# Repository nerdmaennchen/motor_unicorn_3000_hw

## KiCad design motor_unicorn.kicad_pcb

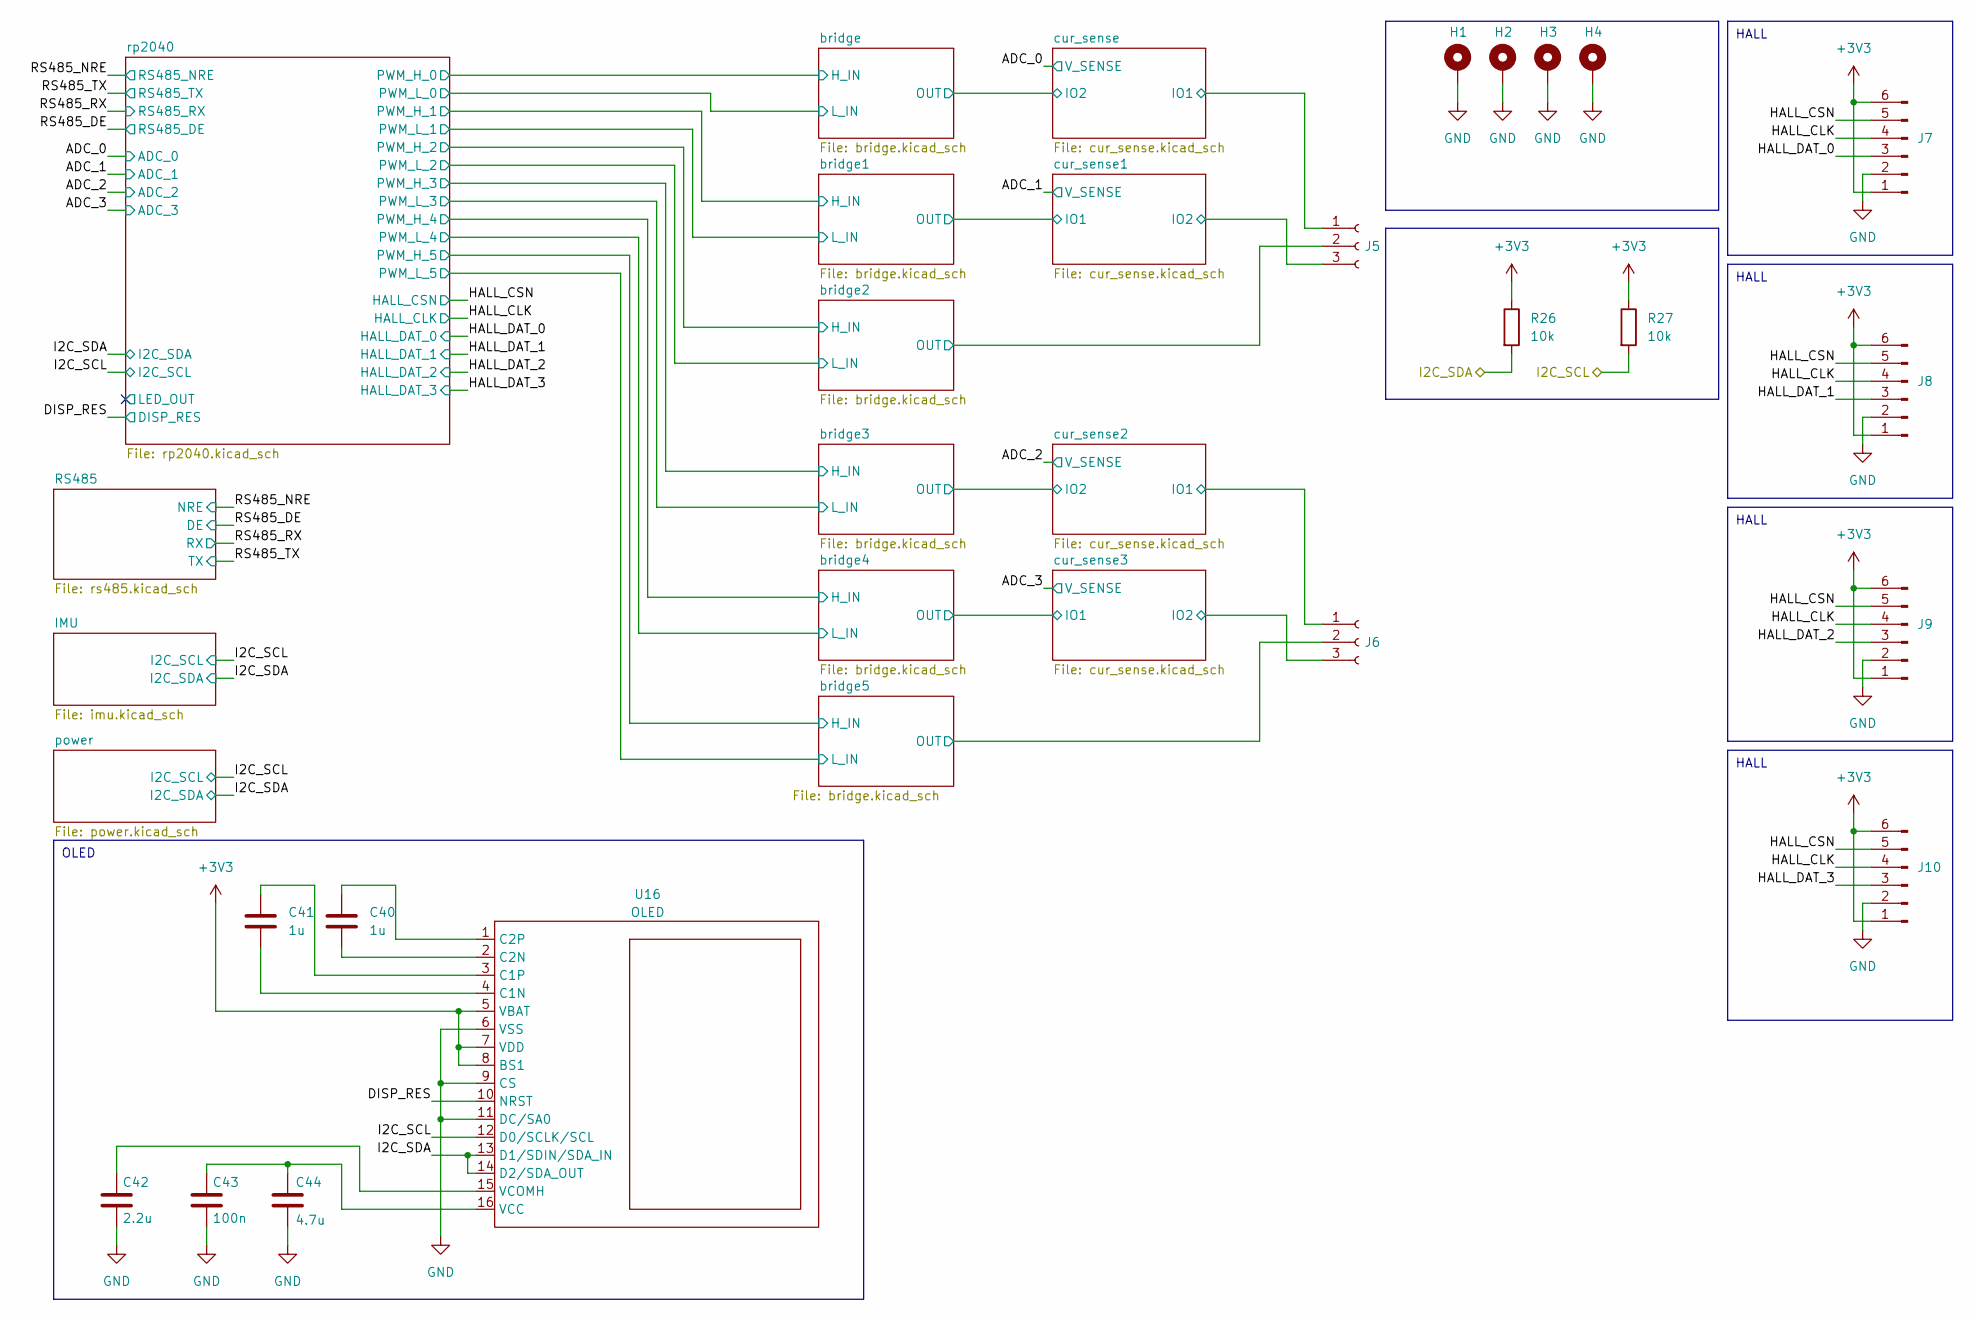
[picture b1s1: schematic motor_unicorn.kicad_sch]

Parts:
C40, C41: 1u; C_0402_1005Metric; LCSC C52923
C42: 2.2u; C_0805_2012Metric; LCSC C12530
C43: 100n; C_0402_1005Metric; LCSC C1525
C44: 4.7u; C_0603_1608Metric; LCSC C19666
H1, H2, H3, H4: MountingHole_Pad; MountingHole_3.2mm_M3_DIN965_Pad_TopBottom
J5, J6: Conn_01x03_Socket; TerminalBlock_Altech_AK300-3_P5.00mm; LCSC C8270
J7, J8, J9, J10: Conn_01x06_Pin; JST_PH_B6B-PH-K_1x06_P2.00mm_Vertical; LCSC C131342
R26, R27: 10k; R_0402_1005Metric; LCSC C25744
U16: OLED

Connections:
+3V3: J7.1, J7.6, J8.1, J8.6, J9.1, J9.6, J10.1, J10.6, R26.1, R27.1, U16.5 (VBAT), U16.7 (VDD), U16.8 (BS1); also elsewhere on the board
/DISP_RES: U16.10 (NRST); also elsewhere on the board
/HALL_CLK: J7.4, J8.4, J9.4, J10.4; also elsewhere on the board
/HALL_CSN: J7.5, J8.5, J9.5, J10.5; also elsewhere on the board
/HALL_DAT_0: J7.3; also elsewhere on the board
/HALL_DAT_1: J8.3; also elsewhere on the board
/HALL_DAT_2: J9.3; also elsewhere on the board
/HALL_DAT_3: J10.3; also elsewhere on the board
/I2C_SCL: R27.2, U16.12 (D0/SCLK/SCL); also elsewhere on the board
/I2C_SDA: R26.2, U16.13 (D1/SDIN/SDA_IN), U16.14 (D2/SDA_OUT); also elsewhere on the board
/bridge2/OUT: J5.2; also elsewhere on the board
/bridge5/OUT: J6.2; also elsewhere on the board
/cur_sense1/IO2: J5.3; also elsewhere on the board
/cur_sense2/IO1: J6.1; also elsewhere on the board
/cur_sense3/IO2: J6.3; also elsewhere on the board
/cur_sense/IO1: J5.1; also elsewhere on the board
GND: C42.2, C43.2, C44.2, H1.1, H2.1, H3.1, H4.1, J7.2, J8.2, J9.2, J10.2, U16.6 (VSS), U16.9 (CS), U16.11 (DC/SA0); also elsewhere on the board
unnamed: C41.2, U16.4 (C1N)
unnamed: C41.1, U16.3 (C1P)
unnamed: C40.2, U16.2 (C2N)
unnamed: C40.1, U16.1 (C2P)
unnamed: C43.1, C44.1, U16.16 (VCC)
unnamed: C42.1, U16.15 (VCOMH)

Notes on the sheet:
HALL
OLED

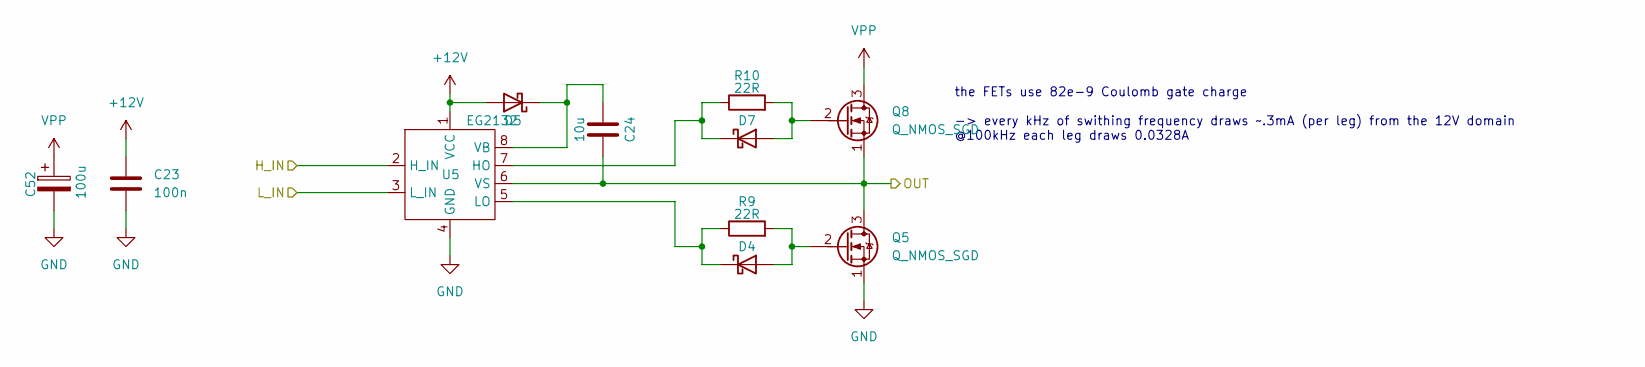
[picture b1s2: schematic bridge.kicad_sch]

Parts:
C23: 100n; C_0402_1005Metric
C24: 10u; C_0603_1608Metric
C52: 100u; CP_Elec_6.3x7.7
D4, D5, D7: D_Schottky; D_SOD-323
Q5, Q8: Q_NMOS_SGD; PQFN-8-EP_6x5mm_P1.27mm_Generic
R9, R10: 22R; R_0402_1005Metric
U5: EG2132; SSOP-8_3.9x5.05mm_P1.27mm

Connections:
+12V: C23.1, D5.2 (A), U5.1 (VCC); also elsewhere on the board
/bridge1/H_IN: U5.2 (H_IN); also elsewhere on the board
/bridge1/L_IN: U5.3 (L_IN); also elsewhere on the board
GND: C23.2, C52.2, Q5.1 (S), U5.4 (GND); also elsewhere on the board
unnamed: D7.1 (K), R10.1, U5.7 (HO)
VPP: C52.1, Q8.3 (D); also elsewhere on the board

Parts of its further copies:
C21, C26, C33, C35, C37: 10u; C_0603_1608Metric
C22, C25, C32, C34, C36: 100n; C_0402_1005Metric
C53, C54, C55, C56, C57: 100u; CP_Elec_6.3x7.7
D3, D6, D8, D9, D10, D11, D12, D13, D14, D15, D16, D17, D18, D19, D20: D_Schottky; D_SOD-323
Q2, Q3, Q4, Q6, Q7, Q9, Q10, Q11, Q12, Q13: Q_NMOS_SGD; PQFN-8-EP_6x5mm_P1.27mm_Generic
R8, R11, R12, R13, R18, R19, R20, R21, R22, R23: 22R; R_0402_1005Metric
U4, U6, U11, U12, U13: EG2132; SSOP-8_3.9x5.05mm_P1.27mm

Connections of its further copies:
+12V: C22.1, C25.1, C32.1, C34.1, C36.1, D6.2 (A), D9.2 (A), D12.2 (A), D15.2 (A), D18.2 (A), U4.1 (VCC), U6.1 (VCC), U11.1 (VCC), U12.1 (VCC), U13.1 (VCC); also elsewhere on the board
/bridge2/H_IN: U6.2 (H_IN); also elsewhere on the board
/bridge2/L_IN: U6.3 (L_IN); also elsewhere on the board
/bridge2/OUT: C26.1, Q4.3 (D), Q10.1 (S), U6.6 (VS); also elsewhere on the board
/bridge3/H_IN: U11.2 (H_IN); also elsewhere on the board
/bridge3/L_IN: U11.3 (L_IN); also elsewhere on the board
/bridge4/H_IN: U12.2 (H_IN); also elsewhere on the board
/bridge4/L_IN: U12.3 (L_IN); also elsewhere on the board
/bridge4/OUT: C35.1, Q6.3 (D), Q12.1 (S), U12.6 (VS); also elsewhere on the board
/bridge5/H_IN: U13.2 (H_IN); also elsewhere on the board
/bridge5/L_IN: U13.3 (L_IN); also elsewhere on the board
/bridge5/OUT: C37.1, Q7.3 (D), Q13.1 (S), U13.6 (VS); also elsewhere on the board
/bridge/H_IN: U4.2 (H_IN); also elsewhere on the board
/bridge/L_IN: U4.3 (L_IN); also elsewhere on the board
GND: C22.2, C25.2, C32.2, C34.2, C36.2, C53.2, C54.2, C55.2, C56.2, C57.2, Q2.1 (S), Q3.1 (S), Q4.1 (S), Q6.1 (S), Q7.1 (S), U4.4 (GND), U6.4 (GND), U11.4 (GND), U12.4 (GND), U13.4 (GND); also elsewhere on the board
unnamed: D3.1 (K), R8.1, U4.7 (HO)
unnamed: D8.2 (A), Q3.2 (G), R11.2
unnamed: C26.2, D9.1 (K), U6.8 (VB)
unnamed: D10.2 (A), Q10.2 (G), R12.2
unnamed: D10.1 (K), R12.1, U6.7 (HO)
unnamed: D11.2 (A), Q4.2 (G), R13.2
unnamed: D11.1 (K), R13.1, U6.5 (LO)
unnamed: C33.2, D12.1 (K), U11.8 (VB)
unnamed: D13.2 (A), Q11.2 (G), R18.2
unnamed: D13.1 (K), R18.1, U11.7 (HO)
unnamed: D14.1 (K), R19.1, U11.5 (LO)
unnamed: C35.2, D15.1 (K), U12.8 (VB)
unnamed: D16.2 (A), Q12.2 (G), R20.2
unnamed: D16.1 (K), R20.1, U12.7 (HO)
unnamed: D17.2 (A), Q6.2 (G), R21.2
unnamed: D17.1 (K), R21.1, U12.5 (LO)
unnamed: C37.2, D18.1 (K), U13.8 (VB)
unnamed: D19.2 (A), Q13.2 (G), R22.2
unnamed: D19.1 (K), R22.1, U13.7 (HO)
unnamed: D20.2 (A), Q7.2 (G), R23.2
unnamed: D20.1 (K), R23.1, U13.5 (LO)
VPP: C53.1, C54.1, C55.1, C56.1, C57.1, Q9.3 (D), Q10.3 (D), Q11.3 (D), Q12.3 (D), Q13.3 (D); also elsewhere on the board

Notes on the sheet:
the FETs use 82e-9 Coulomb gate charge -> every kHz of swithing frequency draws ~.3mA (per leg) from the 12V domain @100kHz each leg draws 0.0328A

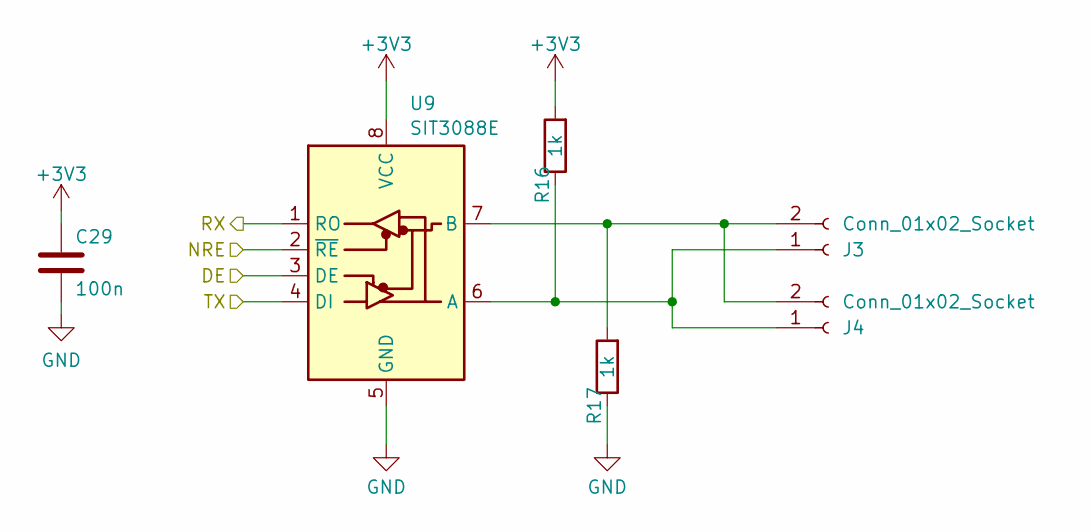
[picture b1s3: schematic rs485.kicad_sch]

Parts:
C29: 100n; C_0402_1005Metric
J3: Conn_01x02_Socket; Molex_PicoBlade_53398-0271_1x02-1MP_P1.25mm_Vertical; LCSC C395343
J4: Conn_01x02_Socket; Molex_PicoBlade_53398-0271_1x02-1MP_P1.25mm_Vertical
R16, R17: 1k; R_0402_1005Metric
U9: SIT3088E; DFN8-3x3mm

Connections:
+3V3: C29.1, R16.2, U9.8 (VCC); also elsewhere on the board
/RS485_DE: U9.3 (DE); also elsewhere on the board
/RS485_NRE: U9.2 (~RE); also elsewhere on the board
/RS485_RX: U9.1 (RO); also elsewhere on the board
/RS485_TX: U9.4 (DI); also elsewhere on the board
GND: C29.2, R17.1, U9.5 (GND); also elsewhere on the board
unnamed: J3.1, J4.1, R16.1, U9.6 (A)
unnamed: J3.2, J4.2, R17.2, U9.7 (B)

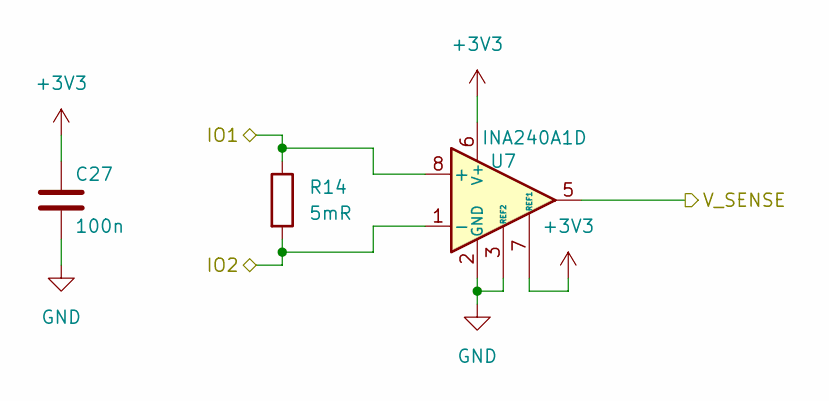
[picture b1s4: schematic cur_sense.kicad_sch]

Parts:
C27: 100n; C_0402_1005Metric
R14: 5mR; R_2512_6332Metric
U7: INA240A1D; SOIC-8_3.9x4.9mm_P1.27mm

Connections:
+3V3: C27.1, U7.6 (V+), U7.7 (REF1); also elsewhere on the board
/ADC_0: U7.5; also elsewhere on the board
/cur_sense/IO1: R14.1, U7.8 (+); also elsewhere on the board
GND: C27.2, U7.2 (GND), U7.3 (REF2), U7.4 (GND); also elsewhere on the board

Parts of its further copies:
C28, C38, C39: 100n; C_0402_1005Metric
R15, R24, R25: 5mR; R_2512_6332Metric
U8, U14, U15: INA240A1D; SOIC-8_3.9x4.9mm_P1.27mm

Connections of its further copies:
+3V3: C28.1, C38.1, C39.1, U8.6 (V+), U8.7 (REF1), U14.6 (V+), U14.7 (REF1), U15.6 (V+), U15.7 (REF1); also elsewhere on the board
/ADC_1: U8.5; also elsewhere on the board
/ADC_2: U14.5; also elsewhere on the board
/ADC_3: U15.5; also elsewhere on the board
/bridge4/OUT: R25.1, U15.8 (+); also elsewhere on the board
/cur_sense1/IO2: R15.2, U8.1 (-); also elsewhere on the board
/cur_sense2/IO1: R24.1, U14.8 (+); also elsewhere on the board
/cur_sense3/IO2: R25.2, U15.1 (-); also elsewhere on the board
GND: C28.2, C38.2, C39.2, U8.2 (GND), U8.3 (REF2), U8.4 (GND), U14.2 (GND), U14.3 (REF2), U14.4 (GND), U15.2 (GND), U15.3 (REF2), U15.4 (GND); also elsewhere on the board

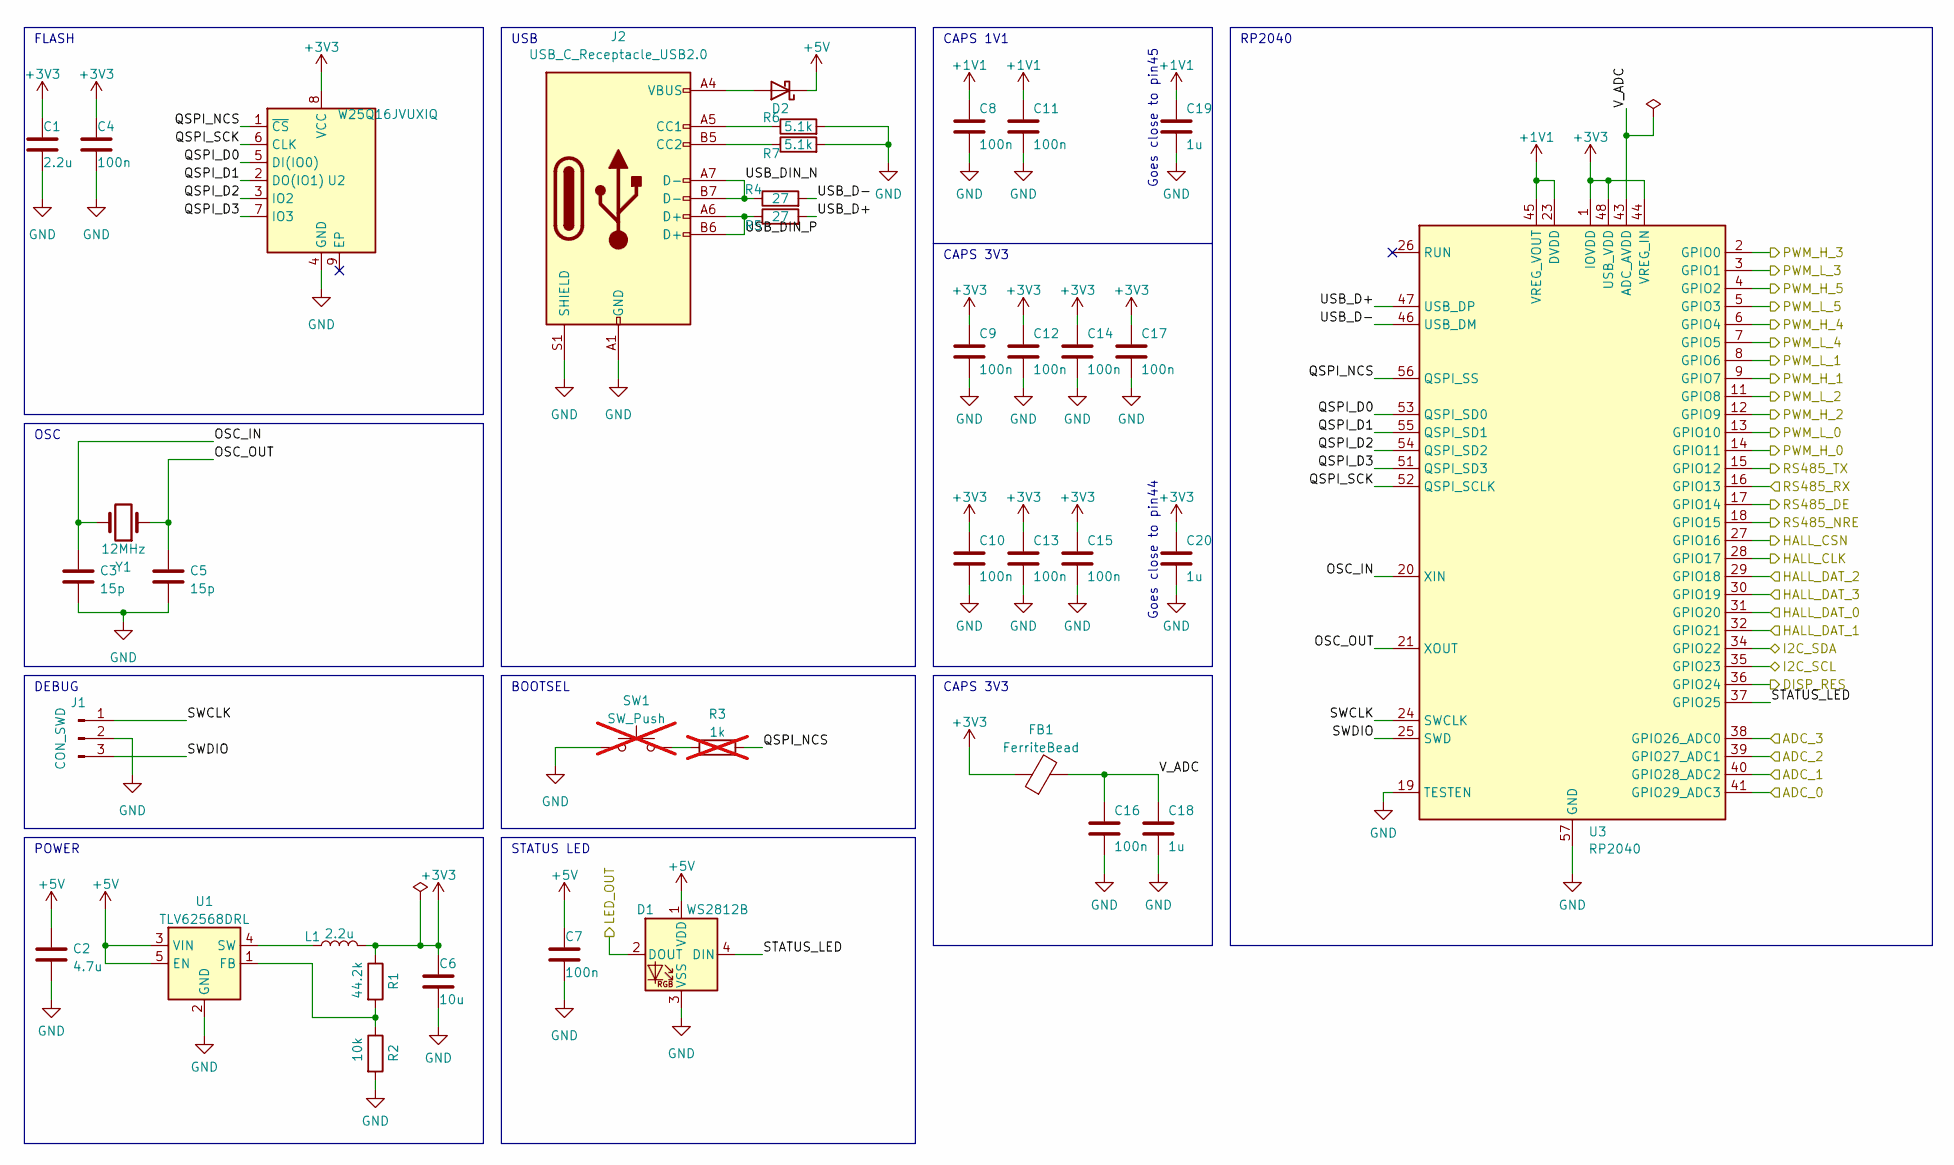
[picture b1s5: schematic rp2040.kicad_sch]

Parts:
C1: 2.2u; C_0402_1005Metric
C2: 4.7u; C_0603_1608Metric
C3, C5: 15p; C_0402_1005Metric
C4, C7, C8, C9, C10, C11, C12, C13, C14, C15, C16, C17: 100n; C_0402_1005Metric
C6: 10u; C_0603_1608Metric
C18, C19, C20: 1u; C_0402_1005Metric
D1: WS2812B; XL-1010RGBC-WS2812B
D2: D_Schottky; D_SOD-323
FB1: FerriteBead; L_0603_1608Metric
J1: CON_SWD; JST_SH_BM03B-SRSS-TB_1x03-1MP_P1.00mm_Vertical
J2: USB_C_Receptacle_USB2.0; USB_C_Receptacle_XKB_U262-16XN-4BVC11
L1: 2.2u; L_0603_1608Metric
R1: 44.2k; R_0402_1005Metric
R2: 10k; R_0402_1005Metric
R3: 1k; R_0402_1005Metric; not fitted
R4, R5: 27; R_0402_1005Metric
R6, R7: 5.1k; R_0402_1005Metric
SW1: SW_Push; SW_Push_1P1T_NO_Vertical_Wuerth_434133025816; not fitted
U1: TLV62568DRL; SOT-563
U2: W25Q16JVUXIQ; DFN-8-1EP_3x2mm_P0.5mm_EP1.3x1.5mm
U3: RP2040; QFN-56-1EP_7x7mm_P0.4mm_EP3.2x3.2mm
Y1: 12MHz; Crystal_SMD_3225-4Pin_3.2x2.5mm

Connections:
+1V1: C8.1, C11.1, C19.1, U3.23 (DVDD), U3.45 (VREG_VOUT), U3.50 (DVDD)
+3V3: C1.1, C4.1, C6.1, C9.1, C10.1, C12.1, C13.1, C14.1, C15.1, C17.1, C20.1, FB1.1, L1.2, R1.1, U2.8 (VCC), U3.1 (IOVDD), U3.10 (IOVDD), U3.22 (IOVDD), U3.33 (IOVDD), U3.42 (IOVDD), U3.44 (VREG_IN), U3.48 (USB_VDD), U3.49 (IOVDD); also elsewhere on the board
+5V: C2.1, C7.1, D1.1 (VDD), D2.1 (K), U1.3 (VIN), U1.5 (EN); also elsewhere on the board
/ADC_0: U3.41 (GPIO29_ADC3); also elsewhere on the board
/ADC_1: U3.40 (GPIO28_ADC2); also elsewhere on the board
/ADC_2: U3.39 (GPIO27_ADC1); also elsewhere on the board
/ADC_3: U3.38 (GPIO26_ADC0); also elsewhere on the board
/DISP_RES: U3.36 (GPIO24); also elsewhere on the board
/HALL_CLK: U3.28 (GPIO17); also elsewhere on the board
/HALL_CSN: U3.27 (GPIO16); also elsewhere on the board
/HALL_DAT_0: U3.31 (GPIO20); also elsewhere on the board
/HALL_DAT_1: U3.32 (GPIO21); also elsewhere on the board
/HALL_DAT_2: U3.29 (GPIO18); also elsewhere on the board
/HALL_DAT_3: U3.30 (GPIO19); also elsewhere on the board
/I2C_SCL: U3.35 (GPIO23); also elsewhere on the board
/I2C_SDA: U3.34 (GPIO22); also elsewhere on the board
/RS485_DE: U3.17 (GPIO14); also elsewhere on the board
/RS485_NRE: U3.18 (GPIO15); also elsewhere on the board
/RS485_RX: U3.16 (GPIO13); also elsewhere on the board
/RS485_TX: U3.15 (GPIO12); also elsewhere on the board
/bridge1/H_IN: U3.9 (GPIO7); also elsewhere on the board
/bridge1/L_IN: U3.8 (GPIO6); also elsewhere on the board
/bridge2/H_IN: U3.12 (GPIO9); also elsewhere on the board
/bridge2/L_IN: U3.11 (GPIO8); also elsewhere on the board
/bridge3/H_IN: U3.2 (GPIO0); also elsewhere on the board
/bridge3/L_IN: U3.3 (GPIO1); also elsewhere on the board
/bridge4/H_IN: U3.6 (GPIO4); also elsewhere on the board
/bridge4/L_IN: U3.7 (GPIO5); also elsewhere on the board
/bridge5/H_IN: U3.4 (GPIO2); also elsewhere on the board
/bridge5/L_IN: U3.5 (GPIO3); also elsewhere on the board
/bridge/H_IN: U3.14 (GPIO11); also elsewhere on the board
/bridge/L_IN: U3.13 (GPIO10); also elsewhere on the board
/rp2040/LED_OUT: D1.2 (DOUT)
/rp2040/OSC_IN: C3.1, U3.20 (XIN), Y1.3 (2)
/rp2040/OSC_OUT: C5.1, U3.21 (XOUT), Y1.1
/rp2040/QSPI_D0: U2.5 (DI(IO0)), U3.53 (QSPI_SD0)
/rp2040/QSPI_D1: U2.2 (DO(IO1)), U3.55 (QSPI_SD1)
/rp2040/QSPI_D2: U2.3 (IO2), U3.54 (QSPI_SD2)
/rp2040/QSPI_D3: U2.7 (IO3), U3.51 (QSPI_SD3)
/rp2040/QSPI_NCS: R3.2, U2.1 (~CS), U3.56 (QSPI_SS)
/rp2040/QSPI_SCK: U2.6 (CLK), U3.52 (QSPI_SCLK)
/rp2040/STATUS_LED: D1.4 (DIN), U3.37 (GPIO25)
/rp2040/SWCLK: J1.1, U3.24 (SWCLK)
/rp2040/SWDIO: J1.3, U3.25 (SWD)
/rp2040/USB_D+: R5.2, U3.47 (USB_DP)
/rp2040/USB_D-: R4.2, U3.46 (USB_DM)
/rp2040/USB_DIN_N: J2.A7 (D-), J2.B7 (D-), R4.1
/rp2040/USB_DIN_P: J2.A6 (D+), J2.B6 (D+), R5.1
/rp2040/V_ADC: C16.1, C18.1, FB1.2, U3.43 (ADC_AVDD)
GND: C1.2, C2.2, C3.2, C4.2, C5.2, C6.2, C7.2, C8.2, C9.2, C10.2, C11.2, C12.2, C13.2, C14.2, C15.2, C16.2, C17.2, C18.2, C19.2, C20.2, D1.3 (VSS), J1.2, J2.A1 (GND), J2.A12 (GND), J2.B1 (GND), J2.B12 (GND), J2.S1 (SHIELD), R2.2, R6.2, R7.2, SW1.1, U1.2 (GND), U2.4 (GND), U3.19 (TESTEN), U3.57 (GND); also elsewhere on the board
unnamed: D2.2 (A), J2.A4 (VBUS), J2.A9 (VBUS), J2.B4 (VBUS), J2.B9 (VBUS)
unnamed: J2.A5 (CC1), R6.1
unnamed: J2.B5 (CC2), R7.1
unnamed: R3.1, SW1.2
unnamed: R1.2, R2.1, U1.1 (FB)
unnamed: L1.1, U1.4 (SW)

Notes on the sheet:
OSC
DEBUG
Goes close to pin45
CAPS 3V3
STATUS LED
BOOTSEL
CAPS 1V1
Goes close to pin44
POWER
RP2040
USB
FLASH

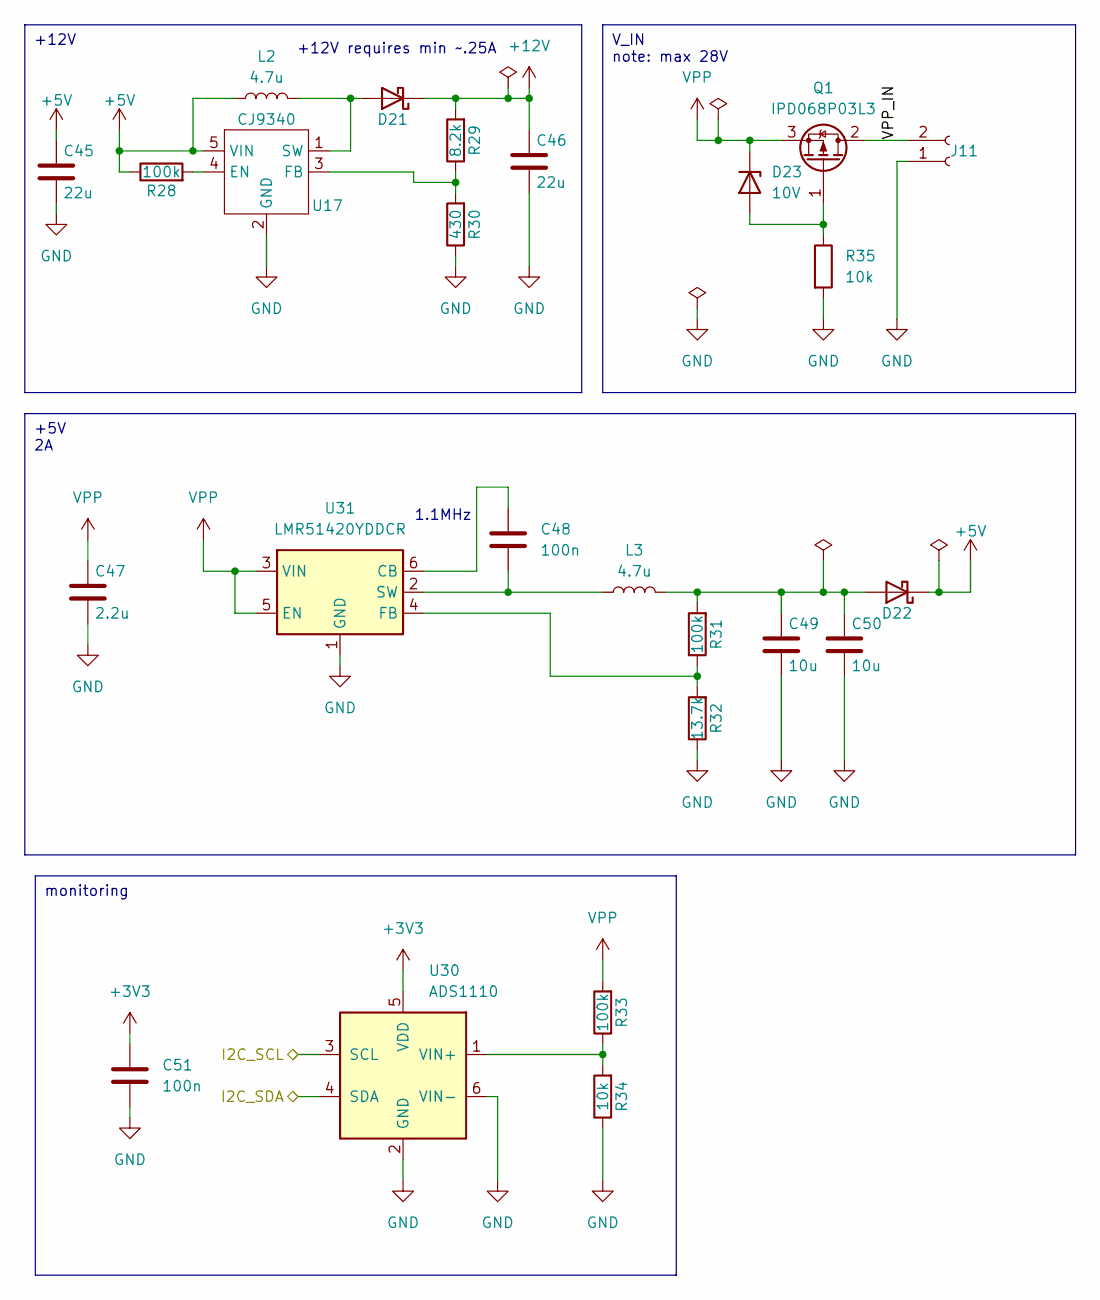
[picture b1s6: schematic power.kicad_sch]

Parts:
C45: 22u; C_0805_2012Metric; LCSC C45783
C46: 22u; C_0805_2012Metric
C47: 2.2u; C_0805_2012Metric
C48, C51: 100n; C_0402_1005Metric
C49, C50: 10u; C_0603_1608Metric
D21, D22: D_Schottky; D_SOD-323
D23: 10V; D_SOD-323
J11: Conn_01x02_Socket; TerminalBlock_bornier-2_P5.08mm
L2, L3: 4.7u; L_0603_1608Metric
Q1: IPD068P03L3; TO-252-2
R28, R31, R33: 100k; R_0402_1005Metric
R29: 8.2k; R_0402_1005Metric
R30: 430; R_0402_1005Metric
R32: 13.7k; R_0402_1005Metric
R34, R35: 10k; R_0402_1005Metric
U17: CJ9340; SOT-23-6
U30: ADS1110; SOT-23-6
U31: LMR51420YDDCR; SOT-23-6

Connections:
+3V3: C51.1, U30.5 (VDD); also elsewhere on the board
+5V: C45.1, D22.1 (K), L2.1, R28.1, U17.5 (VIN); also elsewhere on the board
+12V: C46.1, D21.1 (K), R29.2; also elsewhere on the board
/I2C_SCL: U30.3 (SCL); also elsewhere on the board
/I2C_SDA: U30.4 (SDA); also elsewhere on the board
/power/VPP_IN: J11.2, Q1.2 (D)
GND: C45.2, C46.2, C47.2, C49.2, C50.2, C51.2, J11.1, R30.1, R32.1, R34.1, R35.2, U17.2 (GND), U30.2 (GND), U30.6 (VIN-), U31.1 (GND); also elsewhere on the board
unnamed: D21.2 (A), L2.2, U17.1 (SW)
unnamed: C49.1, C50.1, D22.2 (A), L3.2, R31.2
unnamed: D23.2 (A), Q1.1 (G), R35.1
unnamed: R28.2, U17.4 (EN)
unnamed: R29.1, R30.2, U17.3 (FB)
unnamed: R33.1, R34.2, U30.1 (VIN+)
unnamed: C48.1, U31.6 (CB)
unnamed: R31.1, R32.2, U31.4 (FB)
unnamed: C48.2, L3.1, U31.2 (SW)
VPP: C47.1, D23.1 (K), Q1.3 (S), R33.2, U31.3 (VIN), U31.5 (EN); also elsewhere on the board

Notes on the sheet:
monitoring
V_IN note: max 28V
+5V 2A
+12V
1.1MHz
+12V requires min ~.25A

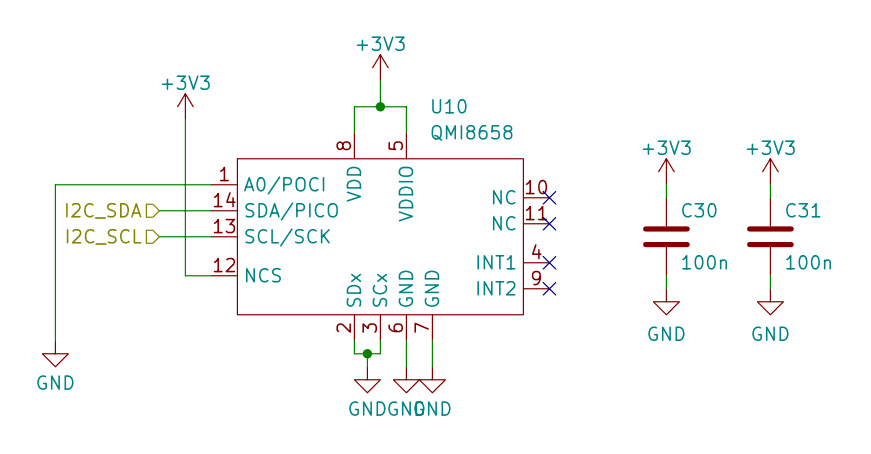
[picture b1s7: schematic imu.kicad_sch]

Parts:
C30, C31: 100n; C_0402_1005Metric
U10: QMI8658; Bosch_LGA-14_3x2.5mm_P0.5mm

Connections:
+3V3: C30.1, C31.1, U10.5 (VDDIO), U10.8 (VDD), U10.12 (NCS); also elsewhere on the board
/I2C_SCL: U10.13 (SCL/SCK); also elsewhere on the board
/I2C_SDA: U10.14 (SDA/PICO); also elsewhere on the board
GND: C30.2, C31.2, U10.1 (A0/POCI), U10.2 (SDx), U10.3 (SCx), U10.6 (GND), U10.7 (GND); also elsewhere on the board

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
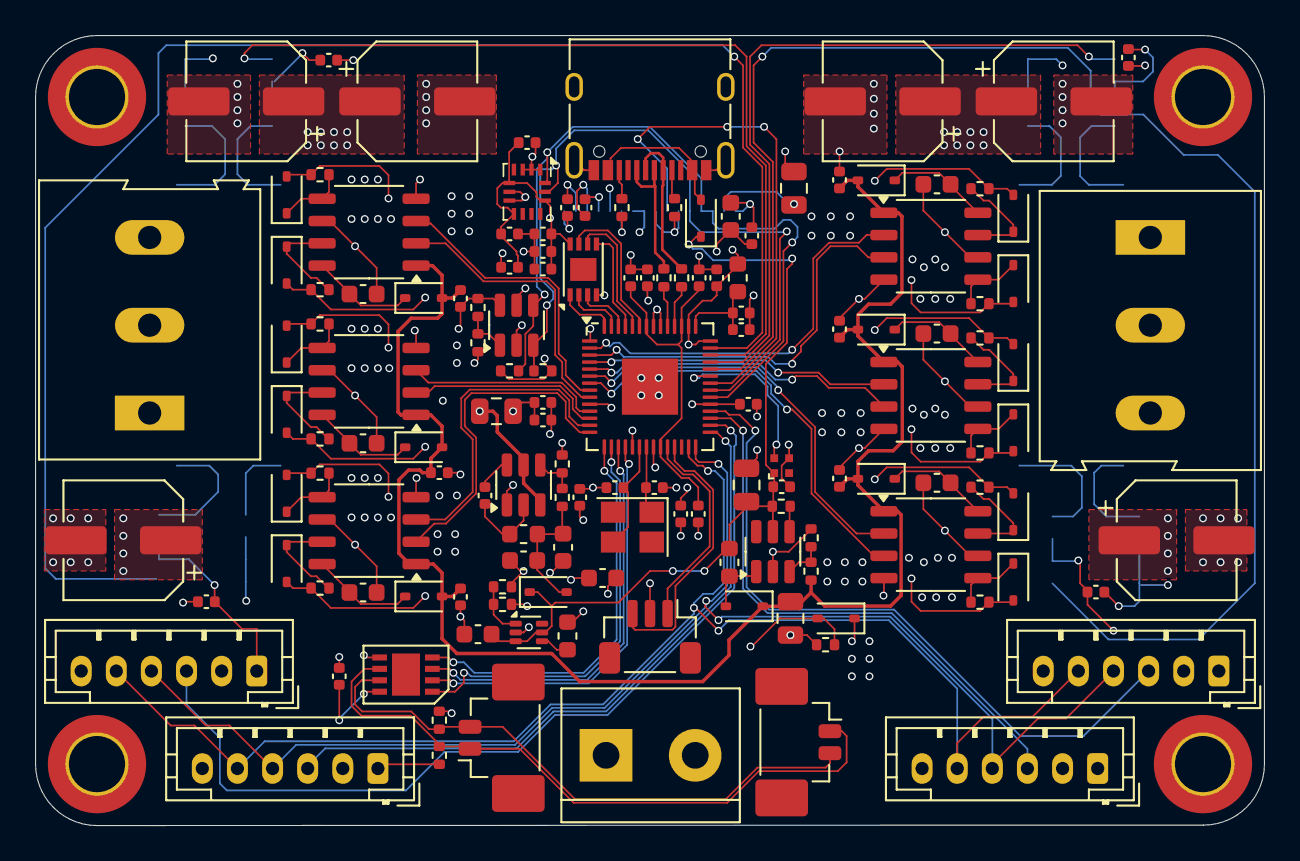
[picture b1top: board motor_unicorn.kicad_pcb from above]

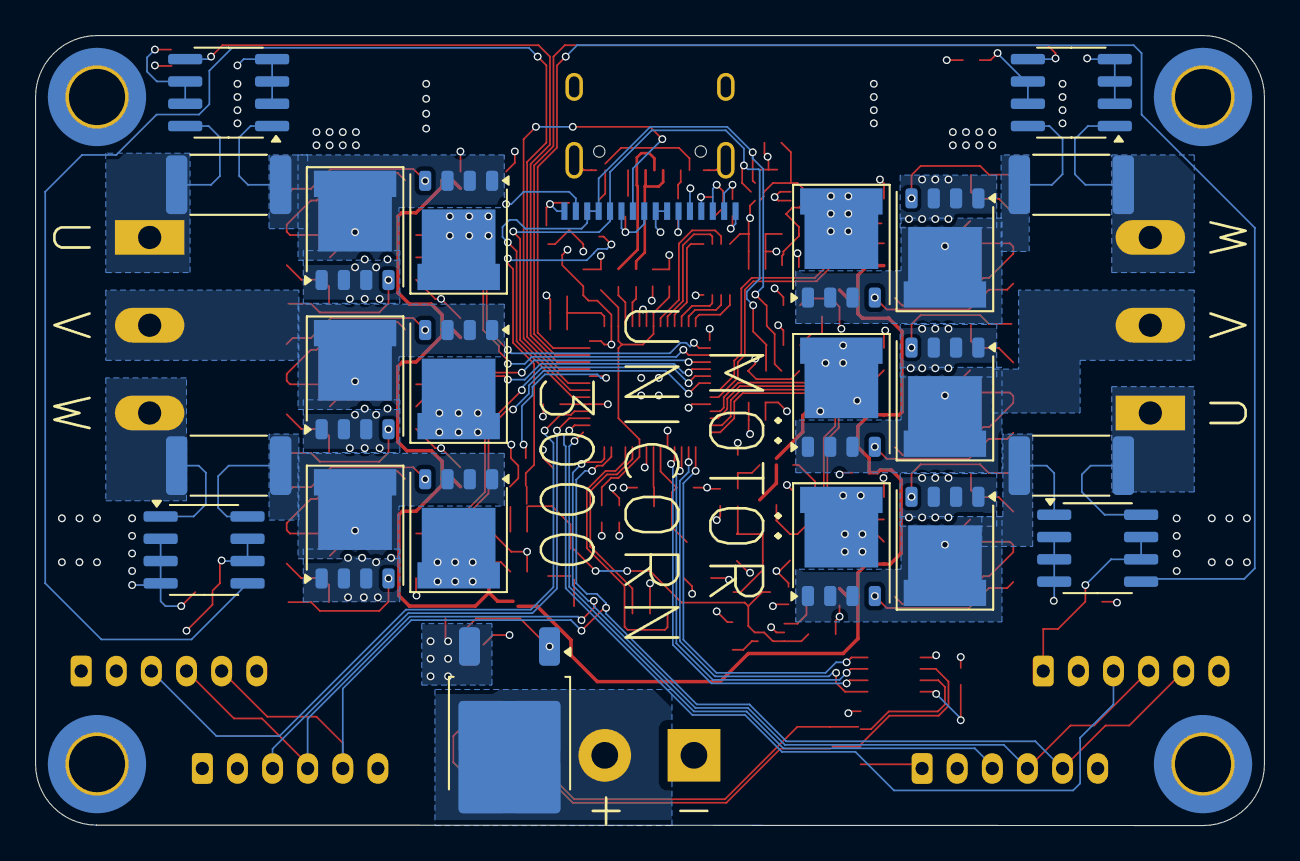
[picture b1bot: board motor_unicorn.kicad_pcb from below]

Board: 4 copper layers, 70.0 x 45.0 mm, 166 parts (22 on the bottom side), 114 nets.

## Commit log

2024-04-02 cleanups and last i2c connections
2024-04-02 more connections
2024-05-04 finalized the design
2024-05-05 ordered version
2024-05-05 tiny last minute fixes
2024-05-06 added an ibom
